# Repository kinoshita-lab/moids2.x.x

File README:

* About
These files are source codes for an artwork "moids 2.0".
You need at least arduino(pro, nano, duemilanove, etc.) or some alternatives to run this program.
We have confirmed this program works on aruduino-0015 version so far.

When you want to know more about moids, please visit our website
http://www.moids.org/

* Instructions
Being Arduino is not a comfortable developping environment for multiple sources, and the author has not arranged some scripts to do this task yet, you need to copy class libraries by hand every time you update sources.

1. Copy the 2 folders, "MsTimer2" , "Moids" to Arduino-****/hardware/libraries/
The destination is depends on where you have installed Arduino.

2. Start Arduino environment and open moids_arduino.pde, compile and upload to I/O board.

* Lisence
These source codes are completely public domain.
You can modify, distribute as you like.

---
Kinoshita-lab 2009

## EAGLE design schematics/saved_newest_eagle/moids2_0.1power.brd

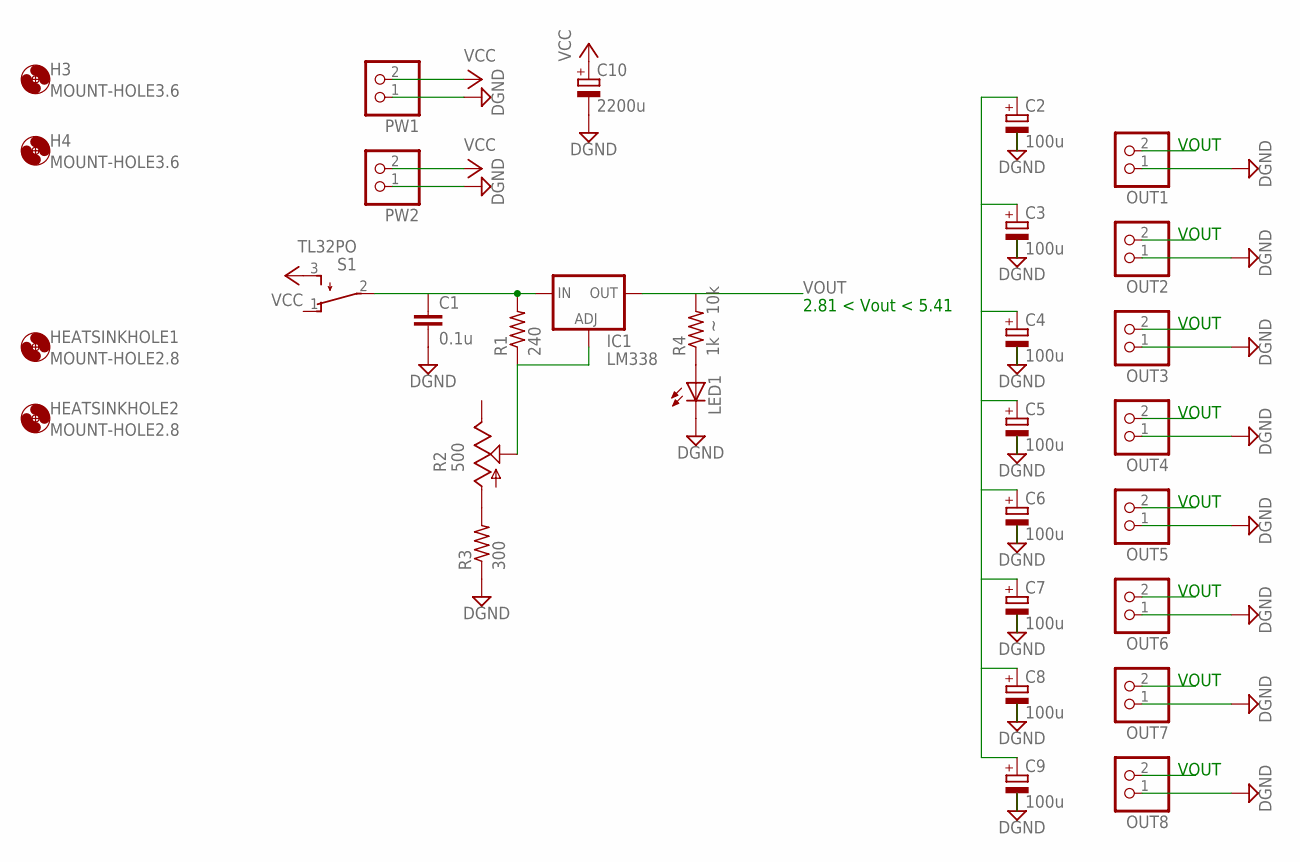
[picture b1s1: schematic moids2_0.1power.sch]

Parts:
C1: 0.1u; C025-024X044
C2, C3, C4, C5, C6, C7, C8, C9: 100u; E2,5-5
C10: 2200u; E7,5-16
H3, H4: MOUNT-HOLE3.6; 3,6
HEATSINKHOLE1, HEATSINKHOLE2: MOUNT-HOLE2.8; 2,8
IC1: LM338; 317TS
LED1: LED3MM
OUT1, OUT2, OUT3, OUT4, OUT5, OUT6, OUT7, OUT8: PINHD-1X2; 1X02
PW1, PW2: PINHD-1X2; 1X02
R1: 240; 0207/2V
R2: 500; B25P
R3: 300; 0207/2V
R4: 1k ~ 10k; 0207/2V
S1: TL32PO; TL3XPO

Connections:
DGND: C1.2, C2.-, C3.-, C4.-, C5.-, C6.-, C7.-, C8.-, C9.-, C10.-, LED1.K (C), OUT1.1, OUT2.1, OUT3.1, OUT4.1, OUT5.1, OUT6.1, OUT7.1, OUT8.1, PW1.1, PW2.1, R3.1
unnamed: IC1.1 (ADJ), R1.1, R2.S
unnamed: R2.A, R3.2
unnamed: LED1.A, R4.1
VCC: C10.+, PW1.2, PW2.2, S1.3 (S)
VIN: C1.1, IC1.3 (IN), R1.2, S1.2
VOUT: C2.+, C3.+, C4.+, C5.+, C6.+, C7.+, C8.+, C9.+, IC1.2 (OUT), OUT1.2, OUT2.2, OUT3.2, OUT4.2, OUT5.2, OUT6.2, OUT7.2, OUT8.2, R4.2

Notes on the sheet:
2.81 < Vout < 5.41
VOUT

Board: 2 copper layers, 31 parts (0 on the bottom side), 7 nets, no tracks yet.

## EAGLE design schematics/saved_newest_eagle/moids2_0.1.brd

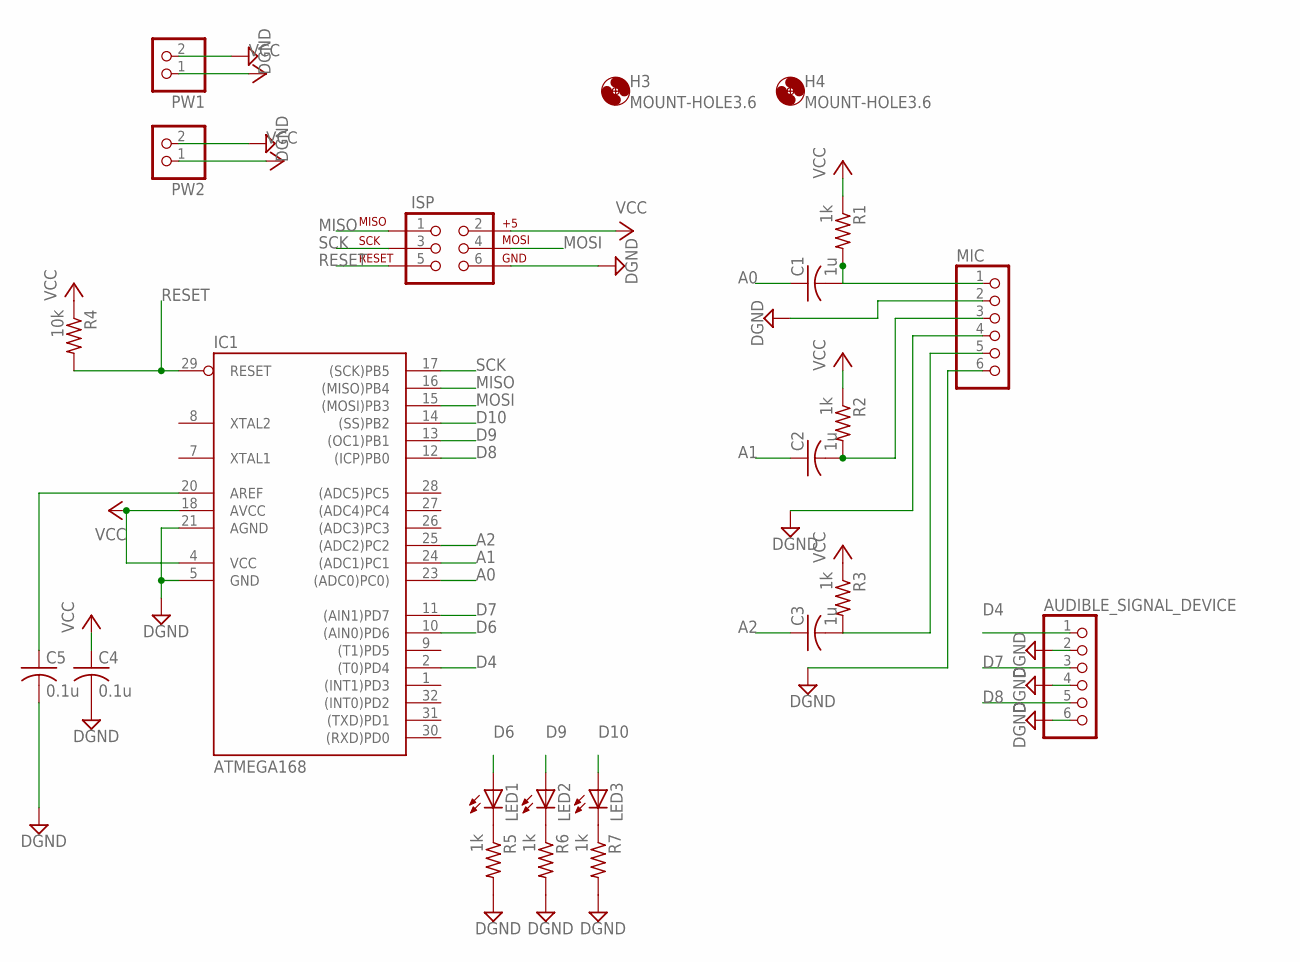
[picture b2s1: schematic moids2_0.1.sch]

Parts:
AUDIBLE_SIGNAL_DEVICE: PINHD-1X6; 1X06
C1, C2, C3: 1u; C1005
C4, C5: 0.1u; C1005
H3, H4: MOUNT-HOLE3.6; 3,6
IC1: ATMEGA168; TQFP32-08
ISP: AVR_SPI_PRG_6PTH; 2X3
LED1, LED2, LED3: LEDCHIPLED_1206; CHIPLED_1206
MIC: PINHD-1X6; 1X06
PW1, PW2: PINHD-1X2; 1X02
R1, R2, R3, R5, R6, R7: 1k; R1005
R4: 10k; R1005

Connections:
A0: C1.1, IC1.23 ((ADC0)PC0))
A1: C2.1, IC1.24 ((ADC1)PC1)
A2: C3.1, IC1.25 ((ADC2)PC2)
AREF: C5.1, IC1.20 (AREF)
D4: AUDIBLE_SIGNAL_DEVICE.1, IC1.2 ((T0)PD4)
D6: IC1.10 ((AIN0)PD6), LED1.A
D7: AUDIBLE_SIGNAL_DEVICE.3, IC1.11 ((AIN1)PD7)
D8: AUDIBLE_SIGNAL_DEVICE.5, IC1.12 ((ICP)PB0)
D9: IC1.13 ((OC1)PB1), LED2.A
D10: IC1.14 ((SS)PB2), LED3.A
DGND: AUDIBLE_SIGNAL_DEVICE.2, AUDIBLE_SIGNAL_DEVICE.4, AUDIBLE_SIGNAL_DEVICE.6, C4.2, C5.2, IC1.5 (GND), IC1.21 (AGND), ISP.6, MIC.2, MIC.4, MIC.6, PW1.2, PW2.2, R5.2, R6.2, R7.2
MISO: IC1.16 ((MISO)PB4), ISP.1
MOSI: IC1.15 ((MOSI)PB3), ISP.4
unnamed: C1.2, MIC.1, R1.2
unnamed: C2.2, MIC.3, R2.2
unnamed: C3.2, MIC.5, R3.2
unnamed: LED1.C, R5.1
unnamed: LED2.C, R6.1
unnamed: LED3.C, R7.1
RESET: IC1.29 (RESET), ISP.5, R4.2
SCK: IC1.17 ((SCK)PB5), ISP.3
VCC: C4.1, IC1.4 (VCC), IC1.18 (AVCC), ISP.2, PW1.1, PW2.1, R1.1, R2.1, R3.1, R4.1

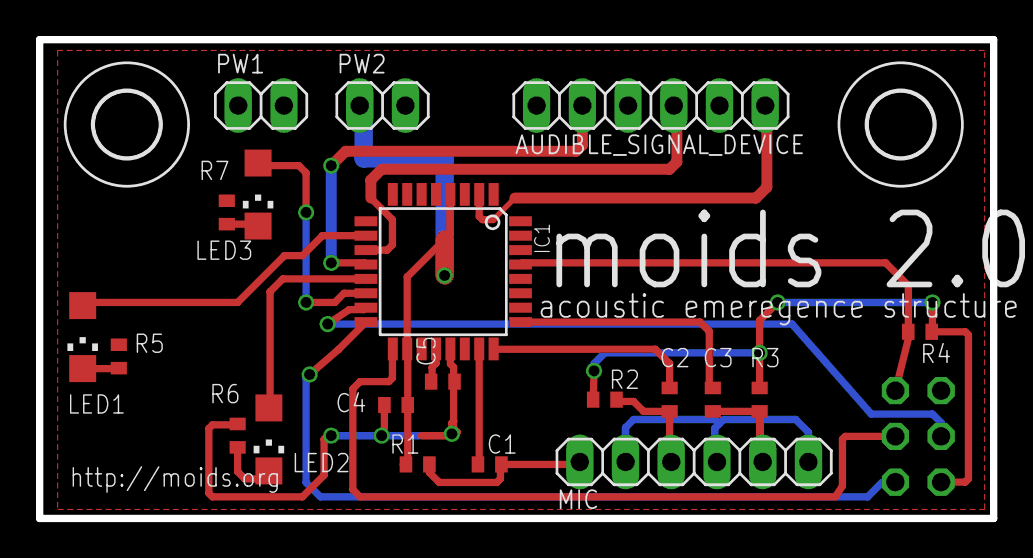
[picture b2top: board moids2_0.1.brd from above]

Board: 2 copper layers, 53.0 x 26.6 mm, 23 parts (1 on the bottom side), 22 nets.

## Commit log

2009-02-17 add main file
2009-02-17 add contents of moids-app(initial implementation)
2009-02-17 add README contents
2009-02-17 github generated gh-pages branch
2009-02-24 add UsTimer2
2009-02-24 remove cpp
2009-02-24 add pde
2009-02-24 added Makefile(saita specific configurations)
2009-02-24 modified pde
2009-05-30 removed ustimer
2009-05-30 add modified MsTimer2
2009-05-30 add moids class
2009-05-30 removed some files...
2009-05-30 modis 2.0 at coded culture version
2009-05-30 add README
2009-05-30 modified README, add instructions, lisence, etc.
2009-05-30 add schematics and board file
2009-05-31 add metalframe pdf made by mhrs
2010-07-17 reduce wait when moids state for yamaguchi 2009
2011-03-05 [schematics]fork moid2_0.1 to make power source schem
2011-03-05 [schematics]made a schem for power source
2011-03-06 [schematics]correct errors, made Power PCB
2011-03-09 [schematics][power]new layout
2011-03-09 [schematics][power]made pcb again
2011-03-22 [schematics][power]mhrs modified version
2011-03-23 [schematics][power]mhrs modified version(correct gnd plane version)
2011-03-23 [schematics][power]correct DRC Check
2011-03-23 [schematics][power]create P-ban garbar data based on http://www.p-ban.com/gerber/eagle.html
2012-01-28 add power schematics and pcb
2012-01-28 add TODO file
2012-01-28 update TODO
2012-01-29 modify folder structure, modify some files for Arduino 1.0
2012-01-29 remove pde file (use ino file)
2012-02-05 format sources
2012-02-05 add random sound table(not yet connected to working programs)
2012-02-05 rename README to make it markdown format
2012-02-05 modify README
2012-02-05 modify README.md again
2012-02-09 modified program for 2.0.3 least specification. varies sound on moids state.
2012-02-11 for 2.2.0 sounding experiment
2012-02-11 free osc mode
2012-03-07 2.0.3 for ZKM
2012-03-08 modify README and TODO, delete non-ascii files, add pdfs for schematics
2012-03-08 add manufacturing instruction
2012-08-19 rename MsTimer2, modifie some files for ease of tweaking(not completed)
2012-08-19 input audio double check feature can be tweaked
2012-08-19 add hex file. its configuration is ATMega168, 8MHz
2012-09-06 undo modification, original spec
2013-01-17 add power and light control feature
2019-07-11 add board
2019-07-11 add power board pdf
2025-11-14 obsolete and move old eagle files
2025-11-14 convert to the latest(and last?) eagle project
2025-11-14 convert latest eagle file to kicad
2025-11-14 add power source 2025(WIP)
2025-11-14 reorganize shchematics folder
2025-11-14 preserve original hex for revising in 2025
2025-11-14 WIP: compile available with arduino 2025(NOT WORKING!)
2025-11-15 WIP, debugging
2025-11-16 update software, confirm working! correct wrong timer counter max for 1sec
2025-11-16 remove test codes
2025-11-16 WIP: directly enter interactive
2025-11-16 directly enter interactive
2025-11-16 remove TOO BIG threshold
2025-11-16 WIP: reducing functions to detect issue
2025-11-17 make moids working only one
2025-11-17 WIP: make timer tick 10 times slower. seems working
2025-11-18 Add extra delay time to meet original specification
2025-11-18 introduce default argment to make void Moids::makeOffset more flexible
2025-11-18 make sampling period constant(125us)
2025-11-18 WIP: 20251118 camp
2025-12-27 2025 power revised
2026-02-04 [wip] remove delay_us
2026-02-05 apply clang-format formatting and refactor code
2026-02-05 [WIP] 20260205 working
2026-02-06 [WIP] remove unpredictable timer behavior
2026-02-06 [RELEASE] 20260206
